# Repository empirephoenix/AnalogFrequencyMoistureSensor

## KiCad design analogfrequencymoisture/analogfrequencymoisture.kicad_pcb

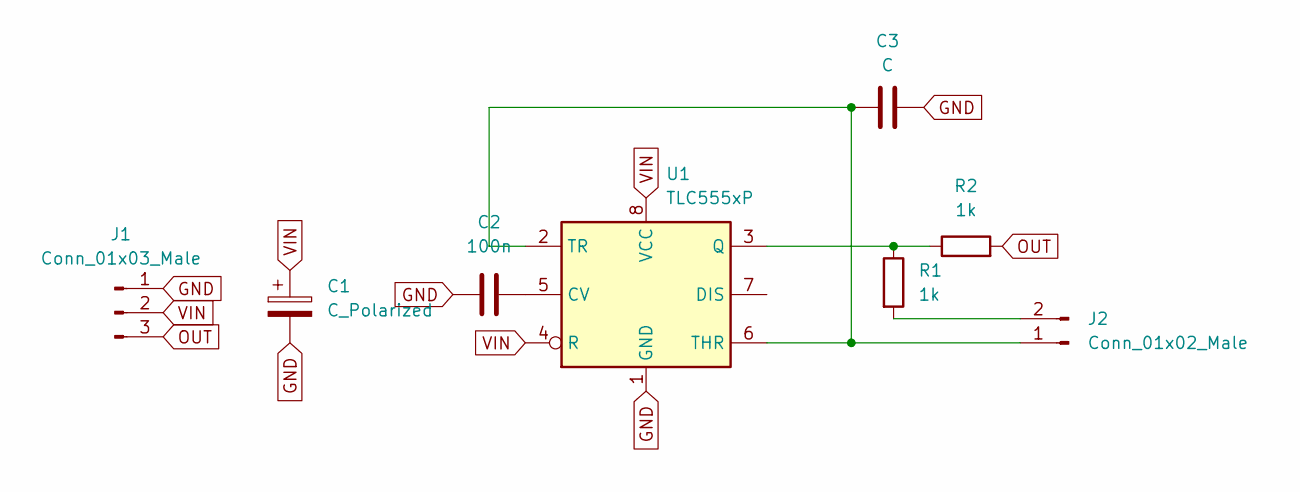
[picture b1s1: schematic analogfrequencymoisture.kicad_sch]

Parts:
C1: C_Polarized; CP_Radial_D8.0mm_P2.50mm
C2: 100n; C_0805_2012Metric
C3: C; C_0805_2012Metric
J1: Conn_01x03_Male; JST_EH_B3B-EH-A_1x03_P2.50mm_Vertical
J2: Conn_01x02_Male; JST_XA_B02B-XASK-1_1x02_P2.50mm_Vertical
R1, R2: 1k; R_0805_2012Metric
U1: TLC555xP; SO-8_3.9x4.9mm_P1.27mm

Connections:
GND: C1.2, C2.1, C3.2, J1.1, U1.1 (GND)
unnamed: C2.2, U1.5 (CV)
unnamed: C3.1, J2.1, U1.2 (TR), U1.6 (THR)
unnamed: J2.2, R1.2
unnamed: R1.1, R2.1, U1.3 (Q)
OUT: J1.3, R2.2
VIN: C1.1, J1.2, U1.4 (R), U1.8 (VCC)

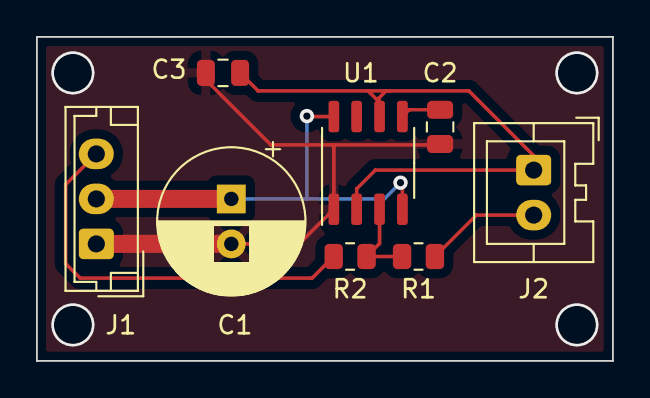
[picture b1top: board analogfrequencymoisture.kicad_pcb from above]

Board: 2 copper layers, 32.0 x 18.0 mm, 8 parts (0 on the bottom side), 7 nets.
